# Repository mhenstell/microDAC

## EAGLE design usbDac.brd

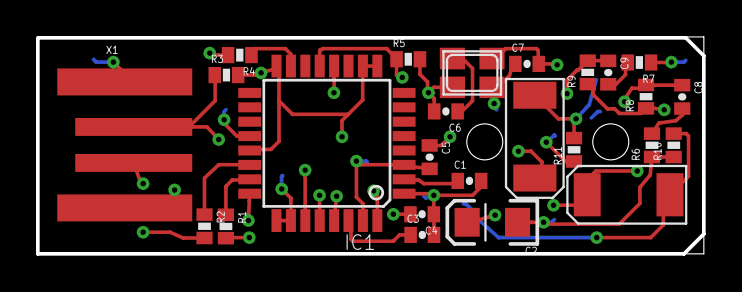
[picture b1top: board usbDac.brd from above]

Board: 4 copper layers, 37.0 x 12.1 mm, 26 parts (1 on the bottom side), 21 nets.

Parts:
C1, C3, C4, C5, C8, C9: 1uF; 0402-CAP
C2: 10uF; EIA3216
C6, C7: 0402-CAP
C10, C11: 100uF; EIA6032
IC1: TQFP32
Q1: NX3225
R1, R2: 22; 0402-RES
R3, R4: 1k5; 0402-RES
R5: 1M; 0402-RES
R6, R7: 16; 0402-RES
R8, R9, R10, R11: 3k3; 0402-RES
U1: AUDIO-JACK-3.5MM-SMD
X1: USBPCB; USB-A-PCB

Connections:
GND: C1.2, C2.C, C3.2, C4.1, C5.2, C7.1, IC1.1, IC1.3, IC1.20, IC1.25, IC1.26, IC1.31, Q1.2, R6.1, R7.1, R8.1, R9.1, R10.1, R11.1, U1.SLEEVE, X1.GND
unnamed: C3.1, IC1.30
unnamed: C1.1, IC1.2
unnamed: C2.A, IC1.32
unnamed: C4.2, IC1.27
unnamed: IC1.23, R1.1
unnamed: IC1.22, R2.1
unnamed: R1.2, R3.1, X1.USB_P
unnamed: R2.2, X1.USB_M
unnamed: C7.2, IC1.13, Q1.3, R5.1
unnamed: IC1.15, R4.1
unnamed: C9.1, C10.P$1, IC1.29, R9.2
unnamed: C6.1, Q1.4
unnamed: C8.1, C11.P$1, IC1.28, R8.2
unnamed: C6.2, IC1.12, Q1.1, R5.2
unnamed: C8.2, R6.2
unnamed: C9.2, R7.2
unnamed: C11.P$2, R10.2, U1.TIP
unnamed: C10.P$2, R11.2, U1.RING
VCC: IC1.24, X1.5V
VDD: C5.1, IC1.9, IC1.10, IC1.16, IC1.21, R3.2, R4.2

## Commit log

2013-03-12 initial
2013-03-12 basic routing
2013-03-14 routed
2013-03-14 moved silkscreen
2013-03-15 had to make it 2-layer cause 4-layer is 5x more expensive :(

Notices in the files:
parts and their libraries:
PCM2706: (c) 2004  Simon Cihelnik
SparkFun-Capacitors: Licensing: CC v3.0 Share-Alike You are welcome to use this library for commercial purposes.
